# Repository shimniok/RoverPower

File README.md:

A high current, 5V power supply for your rover to support your IR rangers, MCU, and more

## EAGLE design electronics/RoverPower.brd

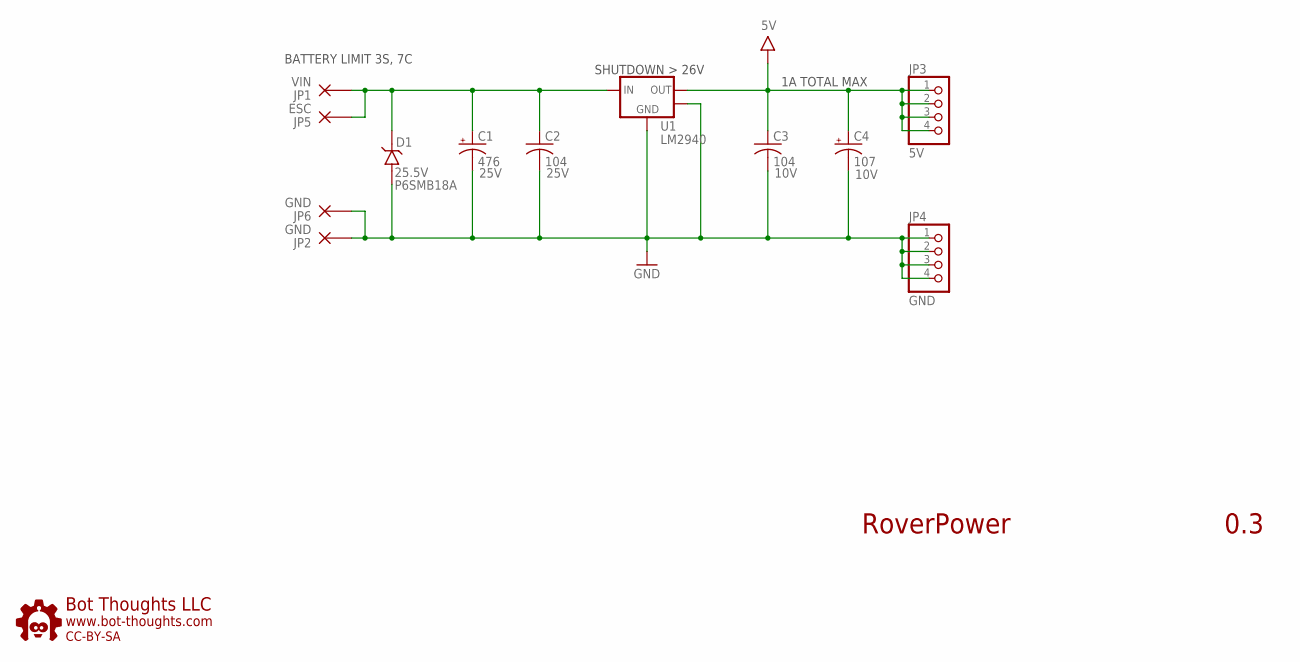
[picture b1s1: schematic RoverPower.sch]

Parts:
C1: 476; E2,5-6; VOLTAGE 25V; PARTNO EEU-FC1H470
C2: 104; C0603; VOLTAGE 25V
C3: 104; C0603; VOLTAGE 10V
C4: 107; SMC_B; VOLTAGE 10V
D1: 25.5V; DO-214AA; PARTNO P6SMB18A
JP1: VIN; PAD_12GA
JP2, JP6: GND; PAD_12GA
JP3: 5V; 1X04-S
JP4: GND; 1X04-S
JP5: ESC; PAD_12GA
U1: LM2940; TO263-3
U$2: BTLOGO-LOGO-MD; BTLOGOM

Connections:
5V: C3.1, C4.+, JP3.1, JP3.2, JP3.3, JP3.4, U1.3 (VOUT)
BAT+: C1.+, C2.1, D1.P$1 (C), JP1.P$1, JP5.P$1, U1.1 (VIN)
GND: C1.-, C2.2, C3.2, C4.-, D1.P$2 (A), JP2.P$1, JP4.1, JP4.2, JP4.3, JP4.4, JP6.P$1, U1.2 (GND), U1.4 (TAB)

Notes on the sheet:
RoverPower
0.3
1A TOTAL MAX
BATTERY LIMIT 3S, 7C
SHUTDOWN > 26V

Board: 2 copper layers, 13 parts (0 on the bottom side), 3 nets, no tracks yet.

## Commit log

2014-01-29 New board for providing 5V power and measuring voltage, amperage.
2014-01-29 Revised traces between bat/esc, added stop mask for tinning. Shrank board size significantly. Added labeling.
2014-01-29 Updated BAT+/ESC+ stop mask
2014-01-29 Fixed Tiny label
2015-05-08 Added README and LICENSE files.
2015-05-12 Eliminated sense, added TVS and larger capacitor for input side voltage spikes, converted to LM2940 automotive regulator, replaced 10uF output cap with Tantalum 100uF, added significant thermal dissi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
2015-05-12 Generated silkscreen
2015-05-12 Added gerbers, zip
2015-05-12 switched wire pads to square
2015-05-12 Readded gerbers and zip
2015-05-12 modified wirepad to square
2016-12-14 copied power polygons to bottom layer, added vias. Changed capacitor to smaller version, revised TVS to higher voltage, changed layout.
2016-12-14 Added more vias, changed output 10uf to .1uf
2016-12-14 updated zip

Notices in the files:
electronics/RoverPower.brd:
cc-by-sa
